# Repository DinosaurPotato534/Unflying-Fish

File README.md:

# Unflying Fish

The main goal of the project was to create a full autonomous underwater vehicle capable of traveling below the surface with no signal. Water completely blocks out both GPS and WIFI, so we will have no connection at all once it submerges below the surface. Thus, the submarine can use gps to navigate above water to various waypoints and use dead-reckoning when navigating underwater.

https://cad.onshape.com/documents/526140a6d93d9e122471a075/w/3eb4851c7e5a9558da121771/e/749db0c17ff4b1f534fcc59e?renderMode=0&uiState=6a8b5b011ef27934121fa507

## Motivation
Both of us (Shaan and Dimitri) have had an interest in amphibious vehicles capable of transferring between water, land, and air. This is one of our first steps in testing underwater systems and learning more about process.

## Design

### Ribbed Hull
For all the 3D printed parts be decided to go with a modular ribbed hull design as it was significantly more efficient in filament. It also greatly reduced support material and made many parts much more printable. The hull works by having a mostly thin outer shell (1.4mm) with several 4mm ribs running across. Then, rings would be nested in these ribs to further support both the walls and anything inside.

### Ballast System
One of the more complicated aspects of the sub was the ballast system. Many other submarines use compressed air to fill a tank, but that requires a pump and only functions a few times before air runs out. Instead, we decided to use a dual approach with a lead screw driving two syringes for precise ballast control. Then, once at the surface and air-pump will fill up plastic bags to push the sub fully out of the water.

### Antenna Tower
The antenna tower is relatively simple, housing both the GPS and ESP-32 Wifi antenna for signal. It also has a window to house LEDs to make the sub more visible when it is barely emerged from the surface.

## Assembling
The main hull consists of a 4in pvc pipe, which everything else will be connected to. Antenna tower, for example, will be epoxied and bolted into the top surface of the pipe, with holes drilled through for wires.

The 3d printed nose will be assembled in multiple smaller parts first. Each quarter will be printed with vertically. Then, the flat ring ribs will be slid down the hull until it reaches its desired spot and epoxied into place. The tail will also be assembled in a similar way.

The electronics bay is a pvc pipe housing all the main electronics, such the battery and flight controller, and will removable from the nose. The nose compartment, which was seen earlier and can be opened, will be close using hose clamps

The end caps for both electronic bays will be 3d printed, but filled with epoxy to seal them. An o-ring will be added on a notch to complete the seal.

The ballast system will be assembled by putting the syringes into custom mounts in the pipe. Then the syringe head will be connected to the lead screw, which is driven by a small dc motor.
The servos controlling the tail flaps will also be in this compartment. They will be sealed by rubber bellows and have push/pull rods leading to the back.

## Electronics
The project features a custom control board with all sensors soldered, with the exception of a few modules which we opted to be breakouts to limit corruption of signal. The board is optimized to limit noise, and includes a ground pour. The board was fully designed in KiCad within the size constraints laid out by CAD.

The craft is powered by an ESP32 S3 with a 4S LiPo battery.

## Software
The projects code will be written in PlatformIO and feature a web-based interface to launch missions, automatic surfacing, and fault-recovery. We will use dead-reckoning to localize the crafts position based on a number of sensors, including custom water flow rate, magnetometer, and gps re-centering on surface. We will account for current using the magnetometer, thrust, and flow rate sensor. The code architecture is fully defined, and the code will be written once the craft is built and verified to ensure efficiency and accuracy.

## Bill Of Materials
| Item | Quantity | Cost (USD) | Purchase Link |
|---|---:|---:|---|
| GPS | 1 | $8.99 | https://www.amazon.com/HiLetgo-GY-NEO6MV2-Controller-Ceramic-Antenna/dp/B01D1D0F5M |
| Hall Effect Sensor | 1 | $3.28 | https://www.aliexpress.us/item/3256808273062702.html |
| Magnets | 1 | $6.45 | https://www.aliexpress.us/item/3256810253099525.html |
| IMU | 1 | $4.84 | https://www.digikey.com/en/products/detail/stmicroelectronics/LSM6DSOTR/9586579 |
| Magnometer | 1 | $5.95 | https://www.adafruit.com/product/5579 |
| Pressure Sensor | 1 | $6.18 | https://www.aliexpress.us/item/3256809434459171.html |
| ESP32-S3 | 1 | $13.99 | https://www.amazon.com/ESP32-S3-DevKitC-1-Development-Dual-Core-Bluetooth/dp/B0GVSHT2Q2 |
| Main Motor | 1 | $29.10 | https://www.underwaterthruster.com/products/apisqueen-brushless-waterproof-motor-2828-12v-16v-500kv-for-underwater-thruster-boat-rov |
| ESC | 1 | $17.64 | https://www.underwaterthruster.com/products/apisqueen-12-24v-3-6s-lipo-45a-bi-directional-esc-to-control-brushless-motors-propellers-in-forward-or-reverse-rotation |
| 4S LIPO | 1 | $26.99 | https://www.amazon.com/OVONIC-Battery-2200mAh-Connector-Quadcopter/dp/B0D8SF1C9K |
| Buck Converter | 1 | $11.20 | https://www.aliexpress.us/item/3256808194722756.html |
| LIPO Converter | 1 | $6.58 | https://www.aliexpress.us/item/3256810183858580.html |
| Wires | 1 | $11.56 | https://www.aliexpress.us/item/3256805055649344.html |
| Resistors | 1 | $6.49 | https://www.amazon.com/Resistor-Resistors-Assortment-Breadboard-Electronics/dp/B0F4P352BB |
| Servos (Pack of 4) | 1 | $17.98 | https://www.amazon.com/Deegoo-FPV-Servo-MG995-Metal-Gear/dp/B07NQJ1VZ2 |
| Breakout (Servos) | 1 | $9.45 | https://www.aliexpress.us/item/3256809858578105.html |
| Power Switch | 1 | $2.27 | https://www.aliexpress.us/item/3256809415854105.html |
| Fuses | 1 | $6.76 | https://www.aliexpress.us/item/3256812122080166.html |
| Capacitors | 1 | $9.99 | https://www.amazon.com/ALLECIN-Electrolytic-Capacitor-Assortment-Kit/dp/B0C1VBXCQM |
| Fuse Mounts | 1 | $11.12 | https://www.aliexpress.us/item/3256808052693050.html |
| Servo Connectors and Crimper | 1 | $24.99 | https://www.amazon.com/Female-Connector-Crimping-Compatible-Spektrum/dp/B0BGX7157Y |
| LEDs | 1 | $8.18 | https://www.aliexpress.us/item/3256806580504872.html |
| Level Shifter for LEDs | 1 | $0.26 | https://www.digikey.com/en/products/detail/diodes-incorporated/74AHCT125S14-13/7724623 |
| GPS Extension Cable | 1 | $6.99 | https://www.amazon.com/POBADY-Female-1-37mm-Low-Loss-Extension/dp/B0C8M8PCJ2 |
| Micro SD Slot | 1 | $2.32 | https://www.digikey.com/en/products/detail/hirose-electric-co-ltd/DM3D-SF/1786510 |
| Decoupling Capacitor | 1 | $2.68 | https://www.aliexpress.us/item/3256811909247133.html |
| Ballast Motor | 2 | $5.93 | https://www.aliexpress.us/item/3256807765699539.html |
| DC Motor Driver | 1 | $2.70 | https://www.digikey.com/en/products/detail/texas-instruments/DRV8833PW/4251165 |
| Ballast Air Motor | 1 | $8.54 | https://www.amazon.com/Jadeshay-Micro-Vacuum-Electric-PumpingBooster/dp/B089ZRYZV8 |
| M3 Screws and Heat Set Inserts | 1 | $15.99 | https://www.amazon.com/Threaded-Inserts-Plastic-3mm-10mm-Pringting/dp/B0GYRQG7F2 |
| PETG | 1 | $46.99 | https://www.amazon.com/SUNLU-PETG-Filament-1-75mm-Printer/dp/B0D1KBQ9VL |
| 4in PVC Pipe | 1 | $30.81 | https://www.homedepot.com/p/Charlotte-Pipe-4-in-x-10-ft-PVC-Schedule-40-DWV-Pipe-PVC074000600/100348477 |
| 3in PVC Pipe | 1 | $21.81 | https://www.homedepot.com/p/Charlotte-Pipe-3-in-x-10-ft-PVC-Schedule-40-Foam-Core-DWV-Pipe-PVC-04300-0600/100348479 |
| Silicone Tubing | 1 | $11.99 | https://www.amazon.com/Hooshing-Silicone-Flexible-Winemaking-Transfer/dp/B08PTXZ51Q |
| Hose Clamps (Tubing) | 1 | $5.19 | https://www.amazon.com/Jersvimc-12pcs-Stainless-Plated-Adjustable/dp/B0BZSKH624 |
| Hose Clamps (Hull) | 1 | $9.99 | https://www.amazon.com/EesTeck-Adjustable-Stainless-Clamps-Ducting/dp/B08B43QT5Y |
| Hose Clamps (Hull) Custom | 1 | $9.99 | https://www.amazon.com/OURU-Clamp-Fasteners-Stainless-Clamps/dp/B0BHZ93JTZ |
| O-Rings | 1 | $8.29 | https://www.amazon.com/XBVV-Nitrile-Assortment-Plumbing-Connections/dp/B0CBTYXVCV |
| Float Balls | 1 | $5.79 | https://www.amazon.com/uxcell-100pcs-Plastic-Bearing-Precision/dp/B0DZWW9C2V |
| Fiberglass Roll | 1 | $12.99 | https://www.amazon.com/Fiberglass-Chopped-Use%EF%BC%8CStrong-Structural-Reinforcement/dp/B0F8TR7Z27 |
| Hose Barb | 1 | $6.39 | https://www.amazon.com/HARFINGTON-Fitting-Splicer-Printing-Compressor/dp/B0FKMMKW9S |
| M4 Heat Set | 1 | $5.99 | https://www.amazon.com/Aoserge-100Pcs-Brass-Heat-Inserts/dp/B0FM3XZZ56 |
| Servo Bellows | 1 | $8.99 | https://www.amazon.com/10Pcs-Waterproof-Push-Rubber-Bellow/dp/B0749L64KJ |
| Syringe | 1 | $9.99 | https://www.amazon.com/Syringe-Without-Needle-Plastic-Syringes/dp/B0C39RWFJZ |
| 4in PVC Pipe O-Ring | 1 | $10.27 | https://www.amazon.com/240-Buna-N-Ring-Durometer-Round/dp/B0051XXMXI |
| 3in PVC Pipe O-Ring | 1 | $6.99 | https://www.amazon.com/uxcell-Nitrile-Automotive-Plumbing-Durometer/dp/B0FNMJNDVR |
| Lead Screws | 1 | $10.04 | https://www.aliexpress.us/item/3256805576723890.html |
| Galvanized Wire | 1 | $7.28 | https://www.amazon.com/Hillman-Galvanized-Solid-Utility-Silver/dp/B00FX982K8 |
| PCB | 1 | $9.00 | Shaan's Cart |
---
| Category | Cost (USD) |
|---|---:|
| AliExpress Shipping | $9.58 |
| Underwater Thruster Shipping | $19.00 |
| DigiKey Shipping | $6.65 |
| Adafruit Shipping | $6.52 |
| Home Depot Shipping | $0.00 |
| Amazon Shipping | $0.00 |
| JLC Shipping | $8.59 |
| **Total (pre-shipping)** | **$540.10** |
| **Total (post-shipping)** | **$590.44** |
---

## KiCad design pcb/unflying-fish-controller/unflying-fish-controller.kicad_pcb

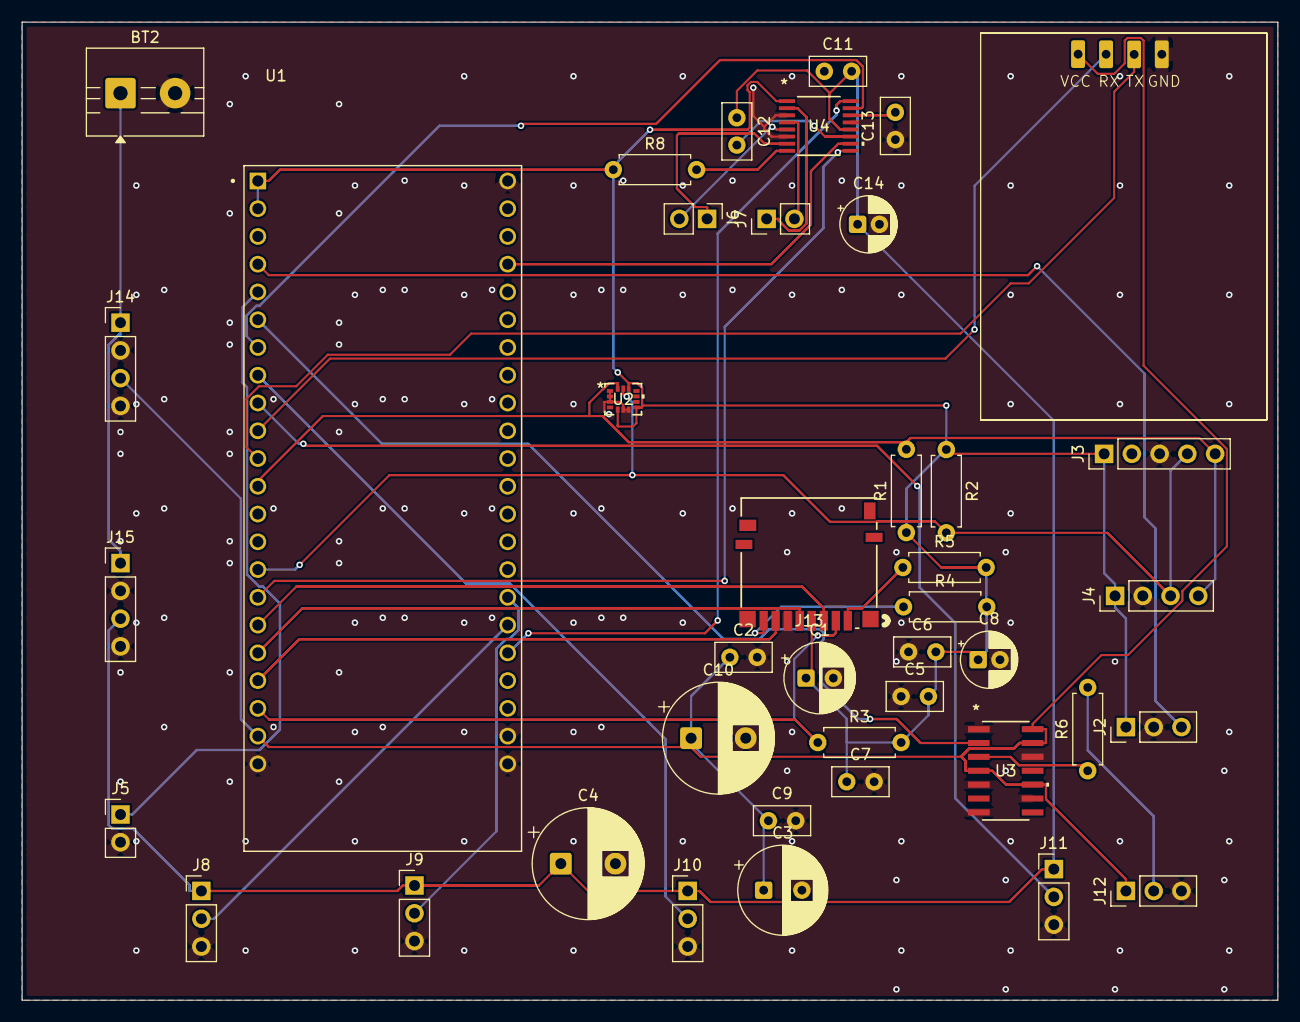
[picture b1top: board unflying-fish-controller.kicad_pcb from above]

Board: 2 copper layers, 114.9 x 89.5 mm, 41 parts (0 on the bottom side), 35 nets.

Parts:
BT2: Battery; TerminalBlock_MaiXu_MX126-5.0-02P_1x02_P5.00mm
C1: 100uF; CP_Radial_D6.3mm_P2.50mm
C2, C7, C9: 100nF; C_Disc_D5.0mm_W2.5mm_P2.50mm
C3: 470uF C; CP_Radial_D8.0mm_P3.50mm
C4, C10: 1000uF; CP_Radial_D10.0mm_P5.00mm
C5, C6: 100nf; C_Disc_D5.0mm_W2.5mm_P2.50mm
C8: 4.7uF; CP_Radial_D5.0mm_P2.00mm
C11: 0.1uF; C_Disc_D5.0mm_W2.5mm_P2.50mm
C12: 10nF; C_Disc_D5.0mm_W2.5mm_P2.50mm
C13: 2.2uF; C_Disc_D5.0mm_W2.5mm_P2.50mm
C14: 10uF; CP_Radial_D5.0mm_P2.00mm
J1: GY-NEO6MV2 (GPS); GY-GPS6MV2
J2: SS49E (Hall Effect Sensor); PinHeader_1x03_P2.54mm_Vertical
J3: MMC5603 (IMU); PinHeader_1x05_P2.54mm_Vertical
J4: GY-MS5837 (MAGENTOMETER); PinHeader_1x04_P2.54mm_Vertical
J5: ESC CAN; PinHeader_1x02_P2.54mm_Vertical
J6: motor2; PinHeader_1x02_P2.54mm_Vertical
J7: motor1; PinHeader_1x02_P2.54mm_Vertical
J8, J9, J10, J11: SERVO; PinHeader_1x03_P2.54mm_Vertical
J12: NEOPIXEL; PinHeader_1x03_P2.54mm_Vertical
J13: DM3D-SF; CONN8_DM3D-SF_HIR
J14: LM2596S (buck converter); PinHeader_1x04_P2.54mm_Vertical
J15: XL4016 (Buck Converter for Servos); PinHeader_1x04_P2.54mm_Vertical
R1, R2: 4.7K; R_Axial_DIN0207_L6.3mm_D2.5mm_P7.62mm_Horizontal
R3, R4, R5, R8: 10k; R_Axial_DIN0207_L6.3mm_D2.5mm_P7.62mm_Horizontal
R6: 330; R_Axial_DIN0207_L6.3mm_D2.5mm_P7.62mm_Horizontal
U1: ESP32-S3-DEVKITC-1-N16R8V
U2: LSM6DSOTR
U3: 74AHCT125S14-13
U4: DRV8833PW; PW16_TEX

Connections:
3V3: C1.1, C5.2, C6.2, C7.1, C8.1, J2.1, J3.1, J4.1, J13.4, R1.1, R2.1, R3.2, R4.2, R5.2, R8.1, U1.J1_1 (3V3), U1.J1_2 (3V3), U2.5 (VDDIO), U2.8 (VDD), U2.12 (CS), U4.1 (NSLEEP)
/+5V: C2.1, C3.1, C9.1, C10.1, J1.26, J12.1, J14.3, U1.J1_21 (5V0), U3.4 (*2OE), U3.10 (*3OE), U3.13 (*4OE), U3.14 (VCC)
/+6V: C4.1, C11.2, C12.1, C14.1, J8.1, J9.1, J10.1, J11.1, J15.3, U4.12 (VM)
/AIN1: U1.J3_18 (GPIO21), U4.16 (AIN1)
/AIN2: U1.J1_7 (GPIO7), U4.15 (AIN2)
/AOUT1: J7.1, U4.2 (AOUT1)
/AOUT2: J7.2, U4.4 (AOUT2)
/BATT+: BT2.1 (+), J14.1, J15.1
/BIN1: U1.J1_16 (GPIO10), U4.9 (BIN1)
/BIN2: U1.J3_4 (GPIO1), U4.10 (BIN2)
/BOUT1: J6.1, U4.7 (BOUT1)
/BOUT2: J6.2, U4.5 (BOUT2)
/ESC_SIG: J5.1, U1.J1_5 (GPIO5)
/GPS_RXD: J1.27, U1.J1_10 (GPIO17)
/GPS_TXD: J1.28, U1.J1_11 (GPIO18)
/HALL_OUT: J2.3, U1.J1_4 (GPIO4)
/NEO_DIN: J12.2, R6.2
/NEO_IN: U1.J1_6 (GPIO6), U3.2 (1A)
/NEO_OUT: R6.1, U3.3 (1Y)
/NFAULT: R8.2, U4.8 (NFAULT)
/SCL: J3.4, J4.3, R2.2, U1.J1_15 (GPIO9), U2.13 (SCL)
/SDA: J3.5, J4.4, R1.2, U1.J1_12 (GPIO8), U2.14 (SDA)
/SD_CS: J13.2, R3.1, U1.J1_20 (GPIO14)
/SD_DAT1: J13.8, R4.1
/SD_DAT2: J13.1, R5.1
/SD_MISO: J13.7, U1.J1_19 (GPIO13)
/SD_MOSI: J13.3, U1.J1_17 (GPIO11)
/SD_SCK: J13.5, U1.J1_18 (GPIO12)
/SERVO1: J8.2, U1.J3_17 (GPIO47)
/SERVO2: J9.2, U1.J3_16 (GPIO48)
/SERVO3: J10.2, U1.J1_8 (GPIO15)
/SERVO4: J11.2, U1.J1_9 (GPIO16)
/VCP: C12.2, U4.11 (VCP)
/VINT: C13.2, U4.14 (VINT)
GND: BT2.2 (-), C1.2, C2.2, C3.2, C4.2, C5.1, C6.1, C7.2, C8.2, C9.2, C10.2, C11.1, C13.1, C14.2, J1.29, J2.2, J3.3, J4.2, J5.2, J8.3, J9.3, J10.3, J11.3, J12.3, J13.6, J14.2, J14.4, J15.2, J15.4, U1.J1_22 (GND), U1.J3_1 (GND), U1.J3_21 (GND), U1.J3_22 (GND), U2.1 (SDO/SA0), U2.2 (SDx), U2.3 (SCx), U2.6 (GND), U2.7 (GND), U3.1 (*1OE), U3.5 (2A), U3.7 (GND), U3.9 (3A), U3.12 (4A), U4.3 (AISEN), U4.6 (BISEN), U4.13 (GND)

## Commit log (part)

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2026-06-13 init
2026-06-14 update BOM
2026-06-16 kicad setup, initial footprints, dimitris ballasts, updated BOM
2026-06-17 minor changes
2026-06-17 BOM update
2026-06-28 new footprints type shit
